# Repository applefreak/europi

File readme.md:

# EuroPi

Put a Pi in your Eurorack! [Hackaday.io Project](https://hackaday.io/project/162308-europi)

## Hardware

Nothing fancy, just a regular 128x32 SSD1306 OLED __i2c__ display and a 24 click (forgot what the right term is) rotatory encoder with switch.

So in my configuration, the two outer pins (on the 3 pins side) of the rotatory encoder goes to GPIO 14 and 15, and one of the swich pin goes to GPIO 4. The middle pin and the other of the switch pin goes to ground. We're talking about __BCM__ GPIO mode here.

OLED display is wired with SDA going to BCM 2 and SCL goes to BCM 3.

If you need a [pinout reference](https://pinout.xyz/).

__Note__ Depending on the type of encoder you get, you might have the different rotation than mine. In this case, simply buy the correct one. OK, I'm joking, just change the code in `encoder_ev` function inside `menu.py` (swap `self.prev()` & `self.next()`, FYI).

## Install

### Dependencies
Uhh I forgot the details, but you need to get your OLED working first.

Check out the tutorial [here](https://learn.adafruit.com/ssd1306-oled-displays-with-raspberry-pi-and-beaglebone-black) and set it up!

After you get that working with their examples, you can clone this repo and run it.

## Run
```
python3 main.py
```

## License

[MIT](https://poyu.mit-license.org/)

BTW, I don't know what to do if I copy and modifies someone else's code (GPLv3, I think) that has a different license. If you know better, please tell me. Thanks!

There's also a font, [DejaVuSans](https://dejavu-fonts.github.io/) I'm distributing here. Hope that's okay under their license. Again, please tell me if you know better.

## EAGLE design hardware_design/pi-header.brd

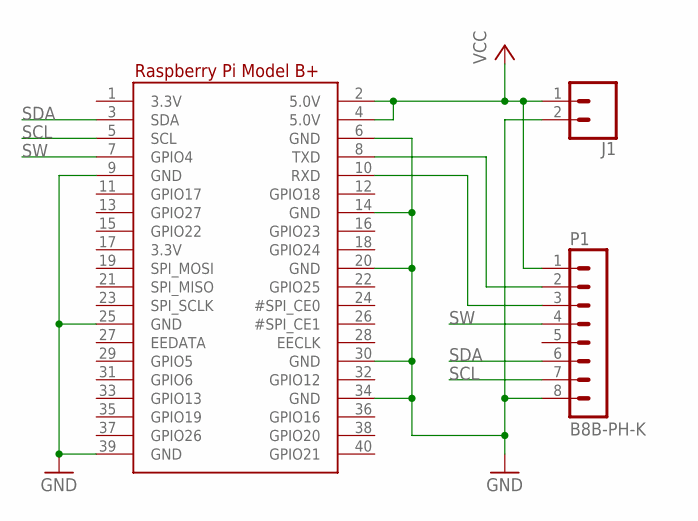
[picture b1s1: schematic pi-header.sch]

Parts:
J1: CONN_02PTH_RA_FEMALE; 1X02_RA_PTH_FEMALE
P1: B8B-PH-K
RPI1: MICROBUILDER_RASPBERRYPI_BPLUS_HATSLOTS; MICROBUILDER_PI_HAT_SLOTS

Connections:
GND: J1.2, P1.8, RPI1.6 (GND), RPI1.9 (GND), RPI1.14 (GND), RPI1.20 (GND), RPI1.25 (GND), RPI1.30 (GND), RPI1.34 (GND), RPI1.39 (GND)
unnamed: P1.2, RPI1.8 (TXD)
unnamed: P1.3, RPI1.10 (RXD)
SCL: P1.7, RPI1.5 (SCL)
SDA: P1.6, RPI1.3 (SDA)
SW: P1.4, RPI1.7 (GPIO4)
VCC: J1.1, P1.1, RPI1.2 (5.0V), RPI1.4 (5.0V)

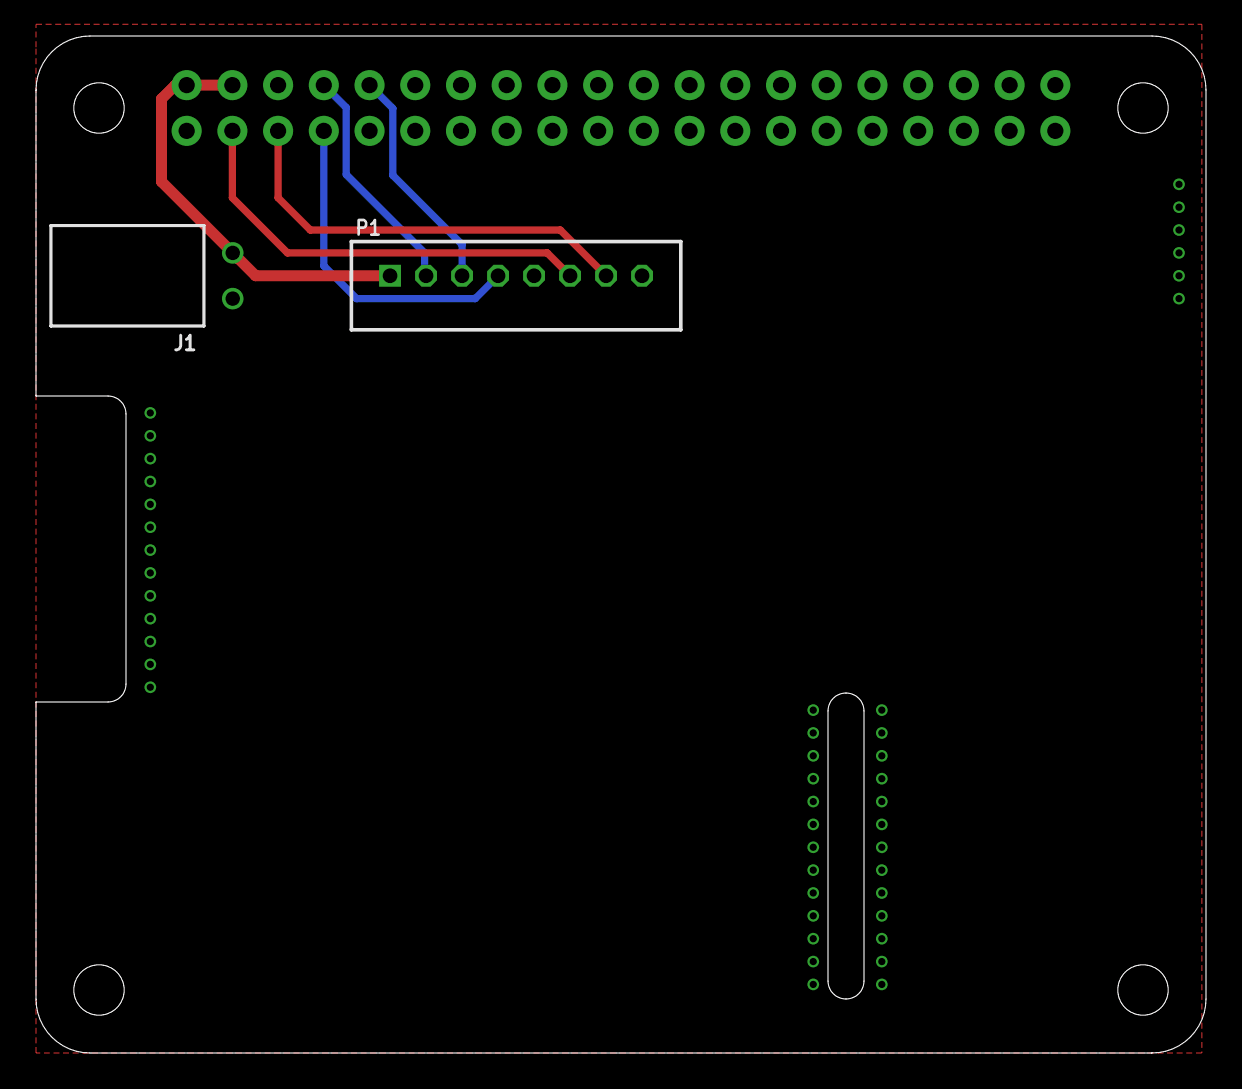
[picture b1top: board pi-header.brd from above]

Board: 2 copper layers, 65.0 x 56.5 mm, 3 parts (0 on the bottom side), 7 nets.

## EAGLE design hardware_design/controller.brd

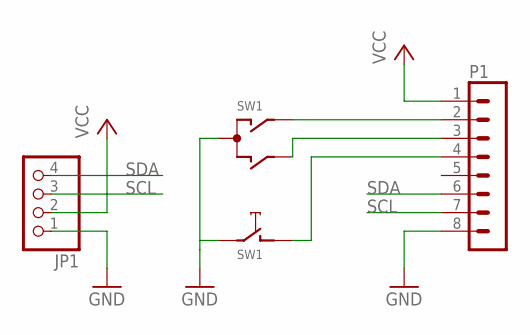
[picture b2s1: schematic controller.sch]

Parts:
JP1: PINHD-1X4; 1X04
P1: B8B-PH-K
SW1: OG-ENCODER_EC12E_SW; OG-ENCODER_ALPS_EC12E_SW

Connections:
GND: JP1.1, P1.8, SW1.C, SW1.E (2)
unnamed: P1.2, SW1.A
unnamed: P1.3, SW1.B
unnamed: P1.4, SW1.D (1)
SCL: JP1.3, P1.7
SDA: JP1.4, P1.6
VCC: JP1.2, P1.1

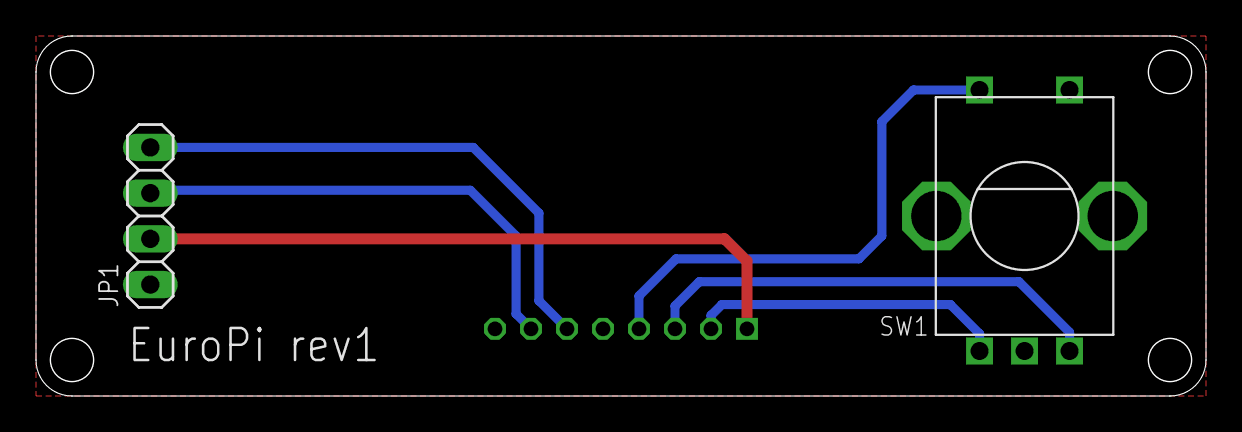
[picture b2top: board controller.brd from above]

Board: 2 copper layers, 64.9 x 19.9 mm, 3 parts (1 on the bottom side), 7 nets.

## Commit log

2018-11-14 MVP code
2018-11-18 controller board
2018-11-22 multi item menu
2018-12-04 add pi-header board, revised controller board

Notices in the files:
parts and their libraries:
con-jst-ph: Copyright (C) 2016, Bob Starr
SparkFun-Connectors: Licensing: Creative Commons ShareAlike 4.0 International - https://creativecommons.org/licenses/by-sa/4.0
